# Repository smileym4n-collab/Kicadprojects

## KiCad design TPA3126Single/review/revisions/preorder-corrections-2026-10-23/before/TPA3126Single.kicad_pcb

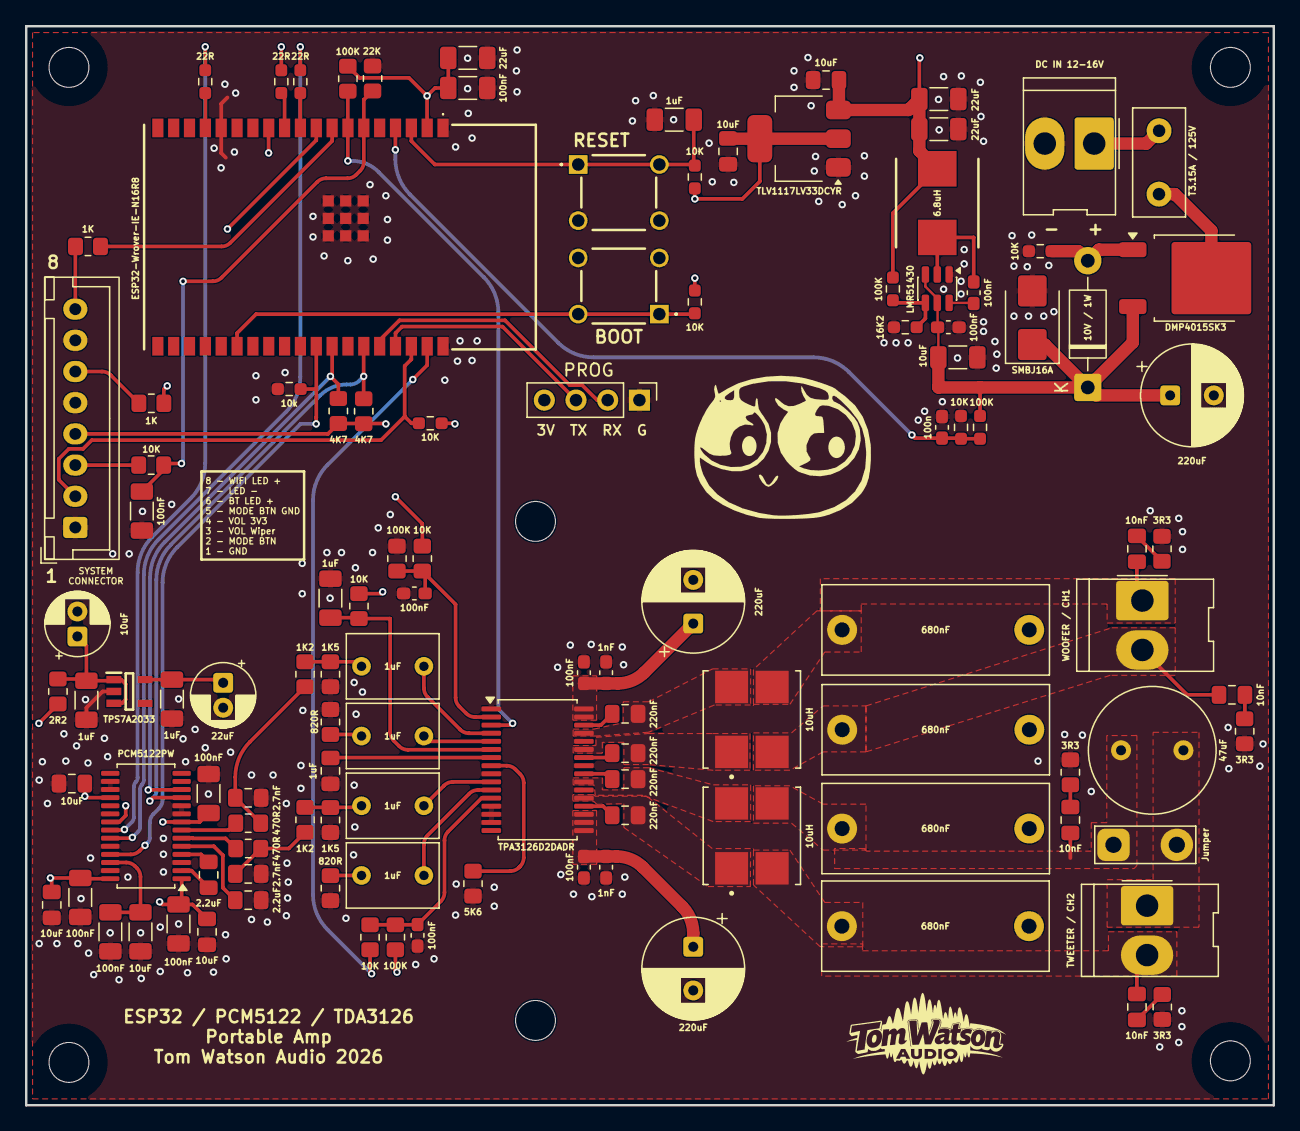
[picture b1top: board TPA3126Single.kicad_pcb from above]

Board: 4 copper layers, 100.0 x 86.5 mm, 120 parts (0 on the bottom side), 74 nets.

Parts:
C1, C2, C5, C6: 1uF; C_Rect_L7.2mm_W5.0mm_P5.00mm
C3, C11, C15, C17, C22, C58: 100nF; C_1206_3216Metric_Pad1.33x1.80mm_HandSolder
C4, C8, C9, C29: 1uF; C_1206_3216Metric_Pad1.33x1.80mm_HandSolder
C7: 10uF; CP_Radial_D5.0mm_P2.00mm
C10: 22uF; CP_Radial_D5.0mm_P2.00mm
C12, C14: 2.2uF; C_0805_2012Metric_Pad1.18x1.45mm_HandSolder
C13, C20, C23, C51, C52: 10uF; C_0805_2012Metric_Pad1.18x1.45mm_HandSolder
C16, C19: 2.7nF; C_0805_2012Metric_Pad1.18x1.45mm_HandSolder
C18, C45: 10uF; C_1206_3216Metric_Pad1.33x1.80mm_HandSolder
C21: 47uF; C_Radial_D10.0mm_H20.0mm_P5.00mm
C24, C25, C26, C27: 220nF; C_0805_2012Metric_Pad1.18x1.45mm_HandSolder
C28: 1uF; C_0805_2012Metric_Pad1.18x1.45mm_HandSolder
C30, C31, C33, C34, C46, C48: 100nF; C_0603_1608Metric_Pad1.08x0.95mm_HandSolder
C32, C54, C59, C60: 10nF; C_0805_2012Metric_Pad1.18x1.45mm_HandSolder
C35, C36, C47: 220uF; CP_Radial_D8.0mm_P3.50mm
C37, C38, C39, C40: 680nF; C_Rect_L18.0mm_W7.0mm_P15.00mm_FKS3_FKP3
C49, C50, C55: 22uF; C_1206_3216Metric_Pad1.33x1.80mm_HandSolder
C53: 100n; C_0603_1608Metric_Pad1.08x0.95mm_HandSolder
C56, C57: 1nF; C_0603_1608Metric_Pad1.08x0.95mm_HandSolder
D1: 10V / 1W; D_DO-41_SOD81_P10.16mm_Horizontal
D2: SMBJ16A; D_SMB
F2: T3.15A / 125V; Fuse_Littelfuse_395Series
H1, H2, H3, H4: MountingHole; MountingHole_3.2mm_M3
HS1: Heatsink; Heatsink_ATS_ATS-TI1OP-521-C1-R1_50x13.9mm_H25mm_P40mm
IC2: RESET; TS026650BK100SCRD
IC3: BOOT; TS026650BK100SCRD
IC4: TPS7A2033; SOT95P280X145-5N
IC5: ESP32-Wrover-IE-N16R8; ESP32-WROVER-IE-N16R8
J1: DC IN 12-16V; Molex_KK-396_5273-02A_1x02_P3.96mm_Vertical
J2: SYSTEM CONNECTOR; JST_XH_B8B-XH-A_1x08_P2.50mm_Vertical
J3: PROG; PinHeader_1x04_P2.54mm_Vertical
J16: WOOFER / CH1; Molex_KK-396_5273-02A_1x02_P3.96mm_Vertical
J17: TWEETER / CH2; Molex_KK-396_5273-02A_1x02_P3.96mm_Vertical
JP1: Jumper; TestPoint_2Pads_Pitch5.08mm_Drill1.3mm
L1: 6.8uH; SRP6030WA-6R8M
L2, L3: 10uH; CSAD0660-100M
Q1: DMP4015SK3; TO-252-2
R1: 2R2; R_0805_2012Metric_Pad1.20x1.40mm_HandSolder
R2, R3: 470R; R_0805_2012Metric_Pad1.20x1.40mm_HandSolder
R4, R5, R9: 22R; R_0603_1608Metric_Pad0.98x0.95mm_HandSolder
R6, R20, R34, R40: 3R3; R_0805_2012Metric_Pad1.20x1.40mm_HandSolder
R7, R8: 1K; R_0805_2012Metric_Pad1.20x1.40mm_HandSolder
R10, R11, R22, R28, R35: 10K; R_0603_1608Metric_Pad0.98x0.95mm_HandSolder
R12, R14: 1K2; R_0805_2012Metric_Pad1.20x1.40mm_HandSolder
R13, R15: 1K5; R_0805_2012Metric_Pad1.20x1.40mm_HandSolder
R16, R17: 820R; R_0805_2012Metric_Pad1.20x1.40mm_HandSolder
R18: 5K6; R_0805_2012Metric_Pad1.20x1.40mm_HandSolder
R19, R21, R26, R39: 10K; R_0805_2012Metric_Pad1.20x1.40mm_HandSolder
R23, R27: 100K; R_0603_1608Metric_Pad0.98x0.95mm_HandSolder
R24: 16K2; R_0603_1608Metric_Pad0.98x0.95mm_HandSolder
R25, R29, R30: 100K; R_0805_2012Metric_Pad1.20x1.40mm_HandSolder
R31, R33: 4K7; R_0805_2012Metric_Pad1.20x1.40mm_HandSolder
R32: 10k; R_0603_1608Metric_Pad0.98x0.95mm_HandSolder
R41: 22K; R_0805_2012Metric_Pad1.20x1.40mm_HandSolder
U1: TPA3126D2DADR; Texas_DAD0032A_HTSSOP-32_6.1x11mm_P0.65mm_TopEP3.71x3.81mm
U2: PCM5122PW; TSSOP-28_4.4x9.7mm_P0.65mm
U3: LMR51430; TSOT-23-6
U4: TLV1117LV33DCYR; SOT-223-3_TabPin2

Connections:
/3V3-ESP: C3.1, C52.1, C55.1, IC5.2 (3V3), J2.4, J3.4, R10.1, R11.1, R19.1, R29.1, R30.1, R31.1, R33.1, R35.2, U4.2 (VO)
/4V_PRE: C49.1, C50.1, C51.1, L1.2, R1.1, R23.1, U4.3 (VI)
/AMP/AMP_ENABLE: IC5.12 (IO27), R21.1
/AMP/AMP_FAULT_N: IC5.7 (IO35), R30.2, U1.3 (FAULTZ)
/AMP/AMP_LINN: C5.2, U1.11 (LINN)
/AMP/AMP_LINP: C6.2, U1.10 (LINP)
/AMP/AMP_MUTE: C31.1, R26.2, R29.2, U1.12 (MUTE)
/AMP/AMP_MUTE_CMD: IC5.37 (IO23), R26.1
/AMP/AMP_RINN: C2.2, U1.5 (RINN)
/AMP/AMP_RINP: C1.2, U1.4 (RINP)
/AMP/AMP_SDZ: C30.1, R21.2, R25.1, U1.2 (SDZ)
/AMP/GAIN_SLV: R18.1, U1.8 (GAIN_SLV)
/AMP/GVDD: C28.1, U1.7 (GVDD)
/AMP/PLIMIT: C29.1, R19.2, U1.6 (PLIMIT)
/AMP/SW_TN: C27.2, L3.1, U1.21 (OUTNL)
/AMP/SW_TP: C26.2, L3.4, U1.23 (OUTPL)
/AMP/SW_WN: C25.2, L2.1, U1.27 (OUTNR)
/AMP/SW_WP: C24.2, L2.4, U1.29 (OUTPR)
/AMP/TWEETER_AUDIO: C16.1, R2.2, R14.1
/AMP/TW_FILTER_P: C21.1, C39.2, C60.1, JP1.1 (A), L3.3
/AMP/TW_PROTECTED_P: C21.2, J17.1, JP1.2 (B)
/AMP/WOOFER_AUDIO: C19.1, R3.1, R12.1
/DAC/AVDD: C9.1, C10.1, C11.1, C13.1, C17.1, C20.1, C22.1, C23.1, IC4.5 (OUT), U2.1 (CPVDD), U2.8 (AVDD), U2.18 (MODE2/MS), U2.28 (DVDD)
/DAC/BCK: R5.1, U2.21 (BCK)
/DAC/DAC_XSMT: IC5.30 (IO18), R32.1, U2.25 (XSMT)
/DAC/DATA: R9.1, U2.22 (DIN)
/DAC/LRCK: R4.1, U2.23 (LRCK)
/ESP32/BT_LED: J2.6, R7.1
/ESP32/EN: C4.1, IC2.1 (NO_1), IC2.2 (NO_2), IC5.3 (EN), R10.2
/ESP32/GPIO0: IC3.1 (NO_1), IC3.2 (NO_2), IC5.25 (IO0), R11.2
/ESP32/MODE BTN: IC5.36 (IO22), J2.2, R35.1
/ESP32/RX: IC5.34 (RXD0), J3.2
/ESP32/SCL: IC5.31 (IO19), R31.2, U2.12 (SCL/MC/ATT1)
/ESP32/SDA: IC5.33 (IO21), R33.2, U2.11 (SDA/MOSI/ATT2)
/ESP32/TX: IC5.35 (TXD0), J3.3
/ESP32/VOL-ADC: C58.1, IC5.6 (IO34), R39.2, R41.1
/ESP32/WIFI_LED: J2.8, R8.1
/PVDD: C33.1, C34.1, C35.1, C36.1, C45.1, C46.1, C47.1, C56.1, C57.1, D1.1 (K), D2.1 (K), Q1.3 (S), R27.1, U1.17 (AVCC), U1.18 (PVCC), U1.19 (PVCC), U1.31 (PVCC), U1.32 (PVCC), U3.3 (VIN), U3.5 (EN)
/VIN_SENSE: C53.1, IC5.4 (SENSOR_VP), R27.2, R28.1
GND: C3.2, C4.2, C7.2, C8.2, C9.2, C10.2, C11.2, C12.2, C13.2, C15.2, C16.2, C17.2, C18.2, C19.2, C20.2, C22.2, C23.2, C28.2, C29.2, C30.2, C31.2, C33.2, C34.2, C35.2, C36.2, C37.1, C38.2, C39.1, C40.2, C45.2, C46.2, C47.2, C49.2, C50.2, C51.2, C52.2, C53.2, C55.2, C56.2, C57.2, C58.2, D2.2 (A), IC2.3 (COM_1), IC2.4 (COM_2), IC3.3 (COM_1), IC3.4 (COM_2), IC4.2 (GND), IC5.1 (GND_1), IC5.15 (GND_2), IC5.38 (GND_3), IC5.39 (GND_4), IC5.40 (GND_5), IC5.41 (GND_6), IC5.42 (GND_7), IC5.43 (GND_8), IC5.44 (GND_9), IC5.45 (GND_10), IC5.46 (GND_11), IC5.47 (GND_12), J1.2, J2.1, J2.5, J2.7, J3.1, R6.2, R13.1, R15.1, R16.1, R17.1, R18.2, R20.2, R22.2, R24.2, R25.2, R28.2, R32.2, R34.2, R40.2, R41.2, U1.1 (MODSEL), U1.9 (GND), U1.13 (AM2), U1.14 (AM1), U1.15 (AM0), U1.22 (GND), U1.25 (GND), U1.28 (GND), U2.3 (CPGND), U2.9 (AGND), U2.10 (VCOM/DEMP), U2.16 (ADR2/GPIO2/DOUT), U2.17 (MODE1), U2.20 (SCK), U2.24 (ADR1/MISO/FMT), U2.27 (DGND), U3.1 (GND), U4.1 (GND)
unnamed: C1.1, R12.2, R13.2
unnamed: C2.1, R16.2
unnamed: C5.1, R17.2
unnamed: C6.1, R14.2, R15.2
unnamed: C32.2, R6.1
unnamed: C54.2, R20.1
unnamed: C59.2, R34.1
unnamed: C60.2, R40.1
unnamed: D1.2 (A), Q1.1 (G), R22.1
unnamed: C7.1, C8.1, IC4.1 (IN), IC4.3 (EN), R1.2
unnamed: IC5.16 (IO13), R9.2
unnamed: IC5.10 (IO25), R4.2
unnamed: IC5.11 (IO26), R5.2
unnamed: IC5.8 (IO32), R8.2
unnamed: IC5.9 (IO33), R7.2
unnamed: F2.1, J1.1
unnamed: J2.3, R39.1
unnamed: C37.2, C54.1, J16.1, L2.3
unnamed: C32.1, C38.1, J16.2, L2.2
unnamed: C40.1, C59.1, J17.2, L3.2
unnamed: F2.2, Q1.2 (D)
unnamed: C27.1, U1.20 (BSNL)
unnamed: C25.1, U1.26 (BSNR)
unnamed: C26.1, U1.24 (BSPL)
unnamed: C24.1, U1.30 (BSPR)
unnamed: C14.2, U2.4 (CAPM)
unnamed: C14.1, U2.2 (CAPP)
unnamed: C15.1, C18.1, U2.26 (LDOO)
unnamed: R2.1, U2.6 (OUTL)
unnamed: R3.2, U2.7 (OUTR)
unnamed: C12.1, U2.5 (VNEG)
unnamed: C48.1, U3.6 (CB)
unnamed: R23.2, R24.1, U3.4 (FB)
unnamed: C48.2, L1.1, U3.2 (SW)

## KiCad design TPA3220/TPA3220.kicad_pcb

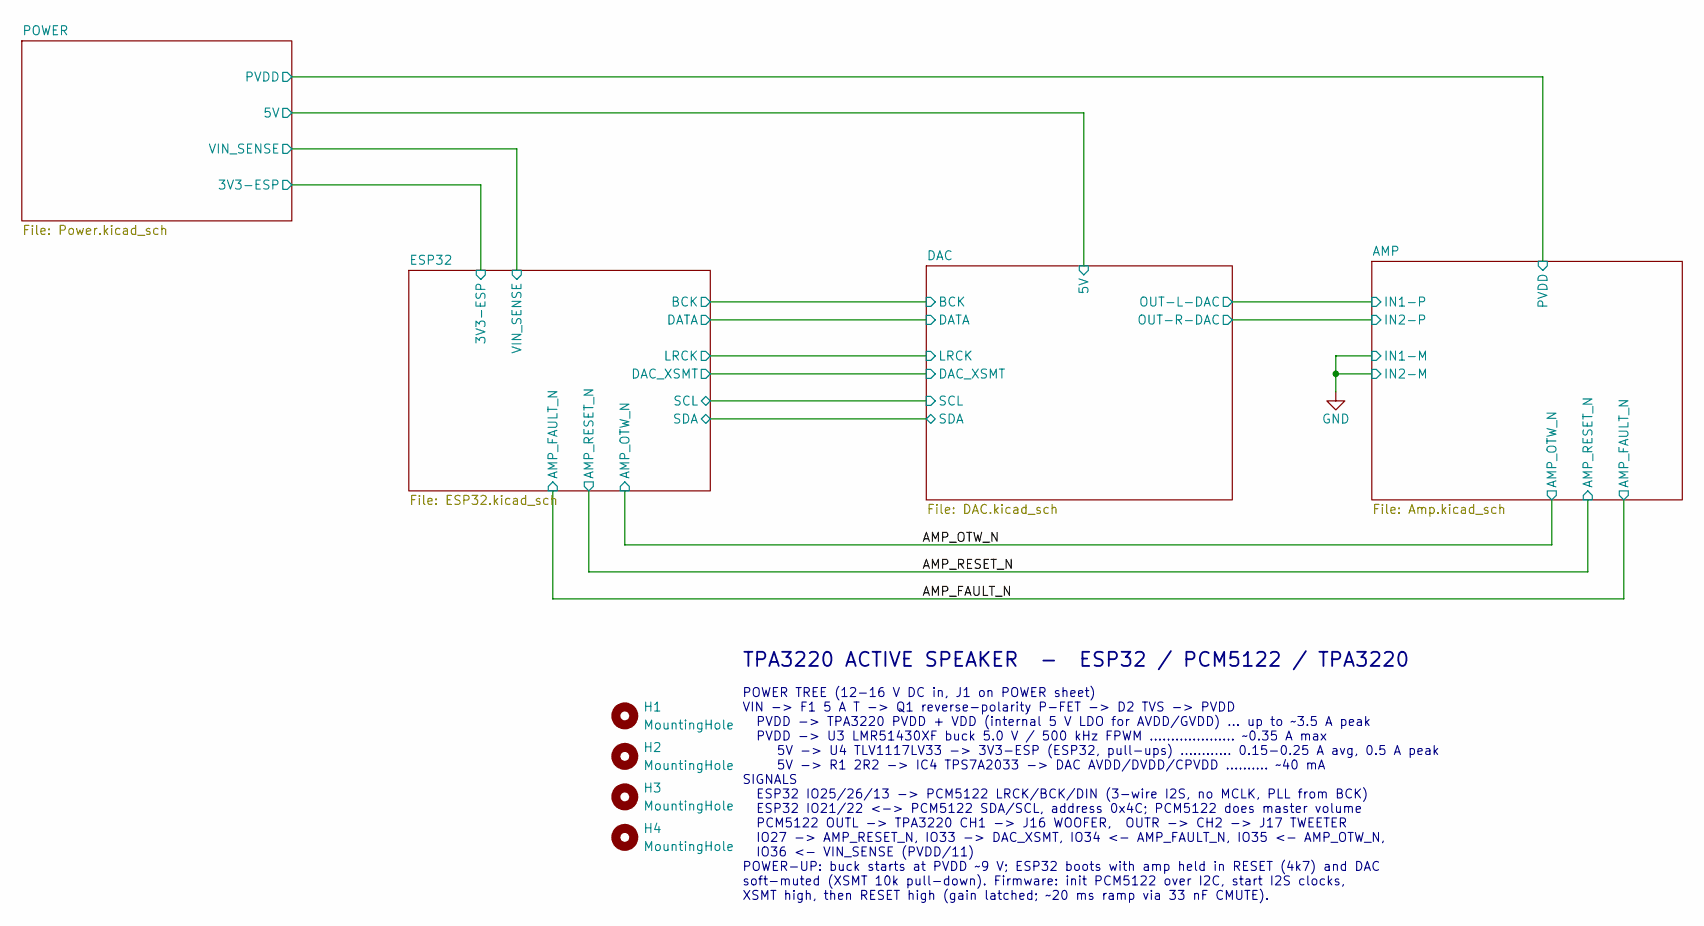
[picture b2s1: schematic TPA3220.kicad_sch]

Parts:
H1, H2, H3, H4: MountingHole; MountingHole_3.2mm_M3

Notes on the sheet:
TPA3220 ACTIVE SPEAKER - ESP32 / PCM5122 / TPA3220
POWER TREE (12-16 V DC in, J1 on POWER sheet) VIN -> F1 5 A T -> Q1 reverse-polarity P-FET -> D2 TVS -> PVDD PVDD -> TPA3220 PVDD + VDD (internal 5 V LDO for AVDD/GVDD) ... up to ~3.5 A peak PVDD -> U3 LMR51430XF buck 5.0 V / 500 kHz FPWM .................... ~0.35 A max 5V -> U4 TLV1117LV33 -> 3V3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

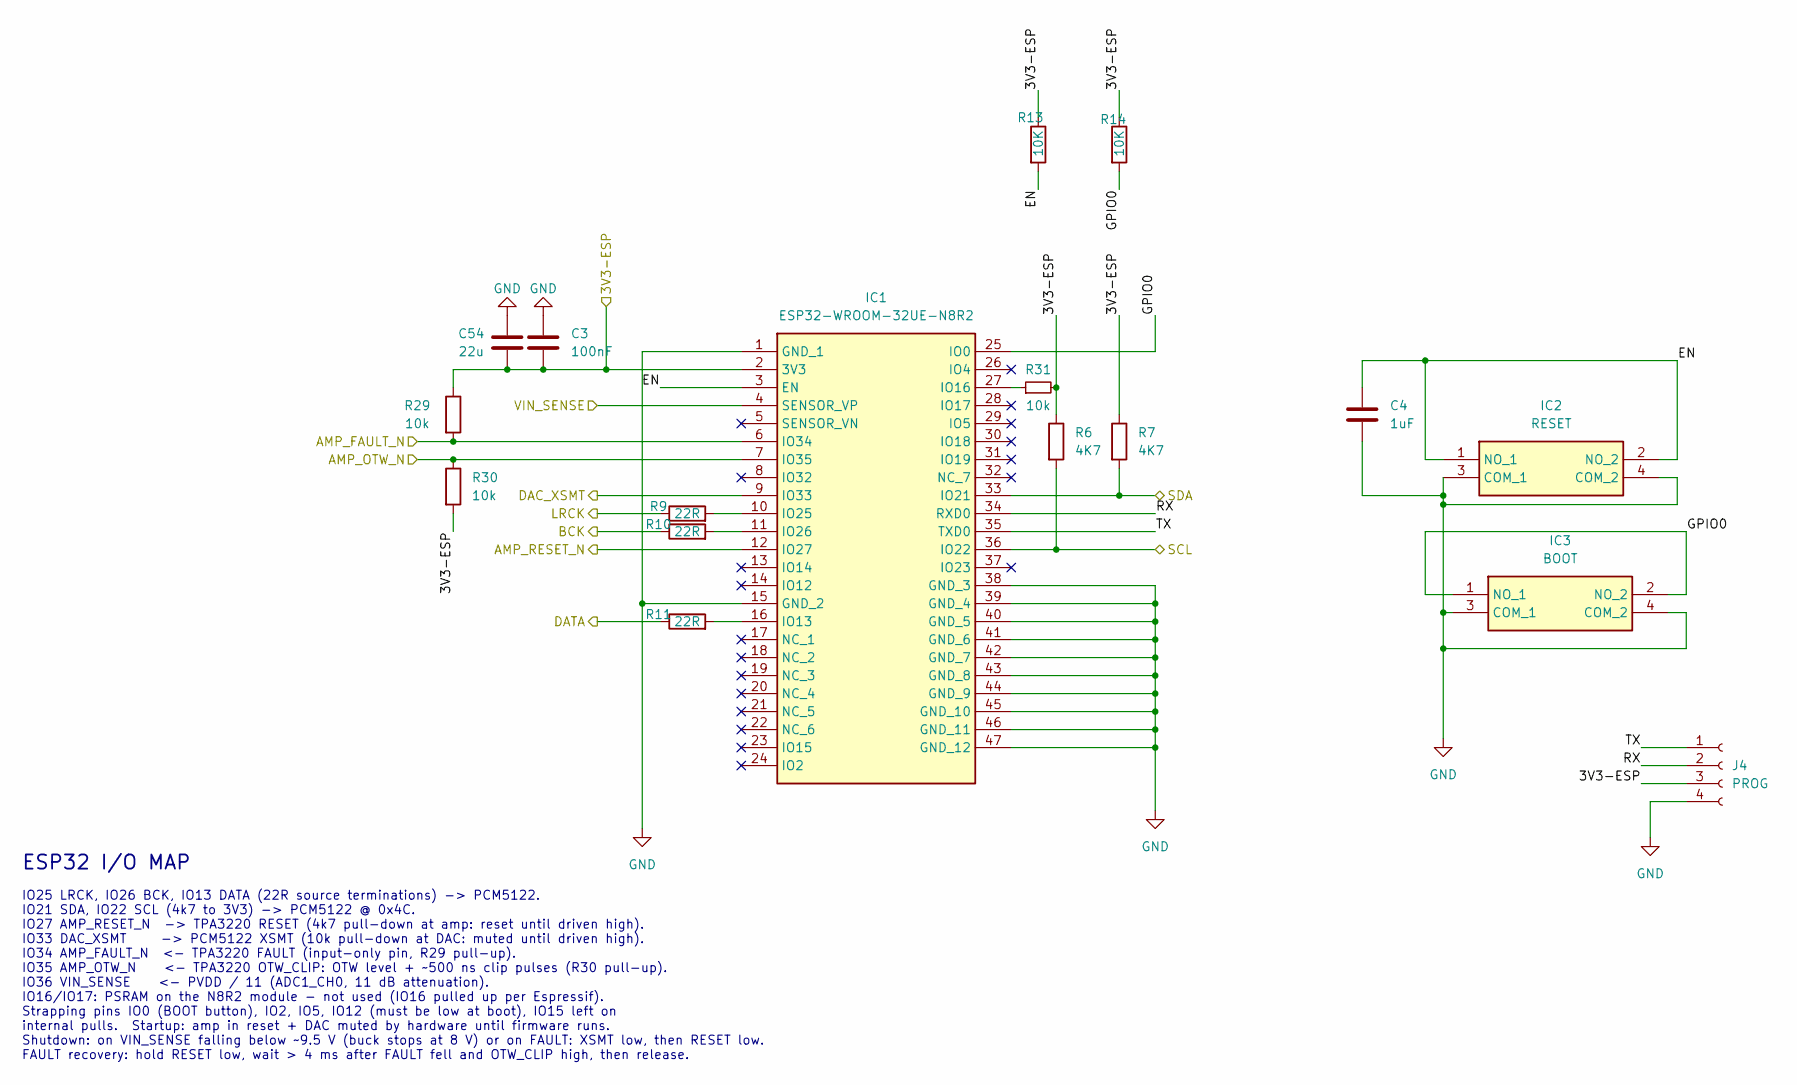
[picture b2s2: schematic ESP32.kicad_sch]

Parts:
C3: 100nF; C_1206_3216Metric_Pad1.33x1.80mm_HandSolder
C4: 1uF; C_1206_3216Metric_Pad1.33x1.80mm_HandSolder
C54: 22u; C_1206_3216Metric_Pad1.33x1.80mm_HandSolder; Manufacturer_Part_Number GRM31CR61E226KE15L
IC1: ESP32-WROOM-32UE-N8R2; ESP32WROOM32UEN8R2; Mouser Part Number 356-ESP32WRM32UEN8R2
IC2: RESET; TS026650BK100SCRD; Mouser Part Number 179-TS026650BK100SCR
IC3: BOOT; TS026650BK100SCRD; Mouser Part Number 179-TS026650BK100SCR
J4: PROG; PinHeader_1x04_P2.54mm_Vertical
R6, R7: 4K7; R_0805_2012Metric_Pad1.20x1.40mm_HandSolder
R9, R10, R11: 22R; R_0603_1608Metric_Pad0.98x0.95mm_HandSolder
R13, R14: 10K; R_0603_1608Metric_Pad0.98x0.95mm_HandSolder
R29, R30, R31: 10k; R_0603_1608Metric_Pad0.98x0.95mm_HandSolder; Manufacturer_Part_Number RC0603FR-0710KL

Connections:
/AMP_FAULT_N: IC1.6 (IO34), R29.2; also elsewhere on the board
/AMP_OTW_N: IC1.7 (IO35), R30.1; also elsewhere on the board
/AMP_RESET_N: IC1.12 (IO27); also elsewhere on the board
/DAC/BCK: R10.1; also elsewhere on the board
/DAC/DAC_XSMT: IC1.9 (IO33); also elsewhere on the board
/DAC/DATA: R11.1; also elsewhere on the board
/DAC/LRCK: R9.1; also elsewhere on the board
/DAC/SCL: IC1.36 (IO22), R6.2; also elsewhere on the board
/DAC/SDA: IC1.33 (IO21), R7.2; also elsewhere on the board
/ESP32/3V3-ESP: C3.2, C54.2, IC1.2 (3V3), J4.3, R6.1, R7.1, R13.1, R14.1, R29.1, R30.2, R31.2; also elsewhere on the board
/ESP32/EN: C4.1, IC1.3 (EN), IC2.1 (NO_1), IC2.2 (NO_2), R13.2
/ESP32/GPIO0: IC1.25 (IO0), IC3.1 (NO_1), IC3.2 (NO_2), R14.2
/ESP32/RX: IC1.34 (RXD0), J4.2
/ESP32/TX: IC1.35 (TXD0), J4.1
/ESP32/VIN_SENSE: IC1.4 (SENSOR_VP); also elsewhere on the board
GND: C3.1, C4.2, C54.1, IC1.1 (GND_1), IC1.15 (GND_2), IC1.38 (GND_3), IC1.39 (GND_4), IC1.40 (GND_5), IC1.41 (GND_6), IC1.42 (GND_7), IC1.43 (GND_8), IC1.44 (GND_9), IC1.45 (GND_10), IC1.46 (GND_11), IC1.47 (GND_12), IC2.3 (COM_1), IC2.4 (COM_2), IC3.3 (COM_1), IC3.4 (COM_2), J4.4; also elsewhere on the board
unnamed: IC1.16 (IO13), R11.2
unnamed: IC1.27 (IO16), R31.1
unnamed: IC1.10 (IO25), R9.2
unnamed: IC1.11 (IO26), R10.2

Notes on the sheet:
ESP32 I/O MAP
IO25 LRCK, IO26 BCK, IO13 DATA (22R source terminations) -> PCM5122. IO21 SDA, IO22 SCL (4k7 to 3V3) -> PCM5122 @ 0x4C. IO27 AMP_RESET_N -> TPA3220 RESET (4k7 pull-down at amp: reset until driven high). IO33 DAC_XSMT -> PCM5122 XSMT (10k pull-down at DAC: muted until driven high). IO34 AMP_FAULT_N 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

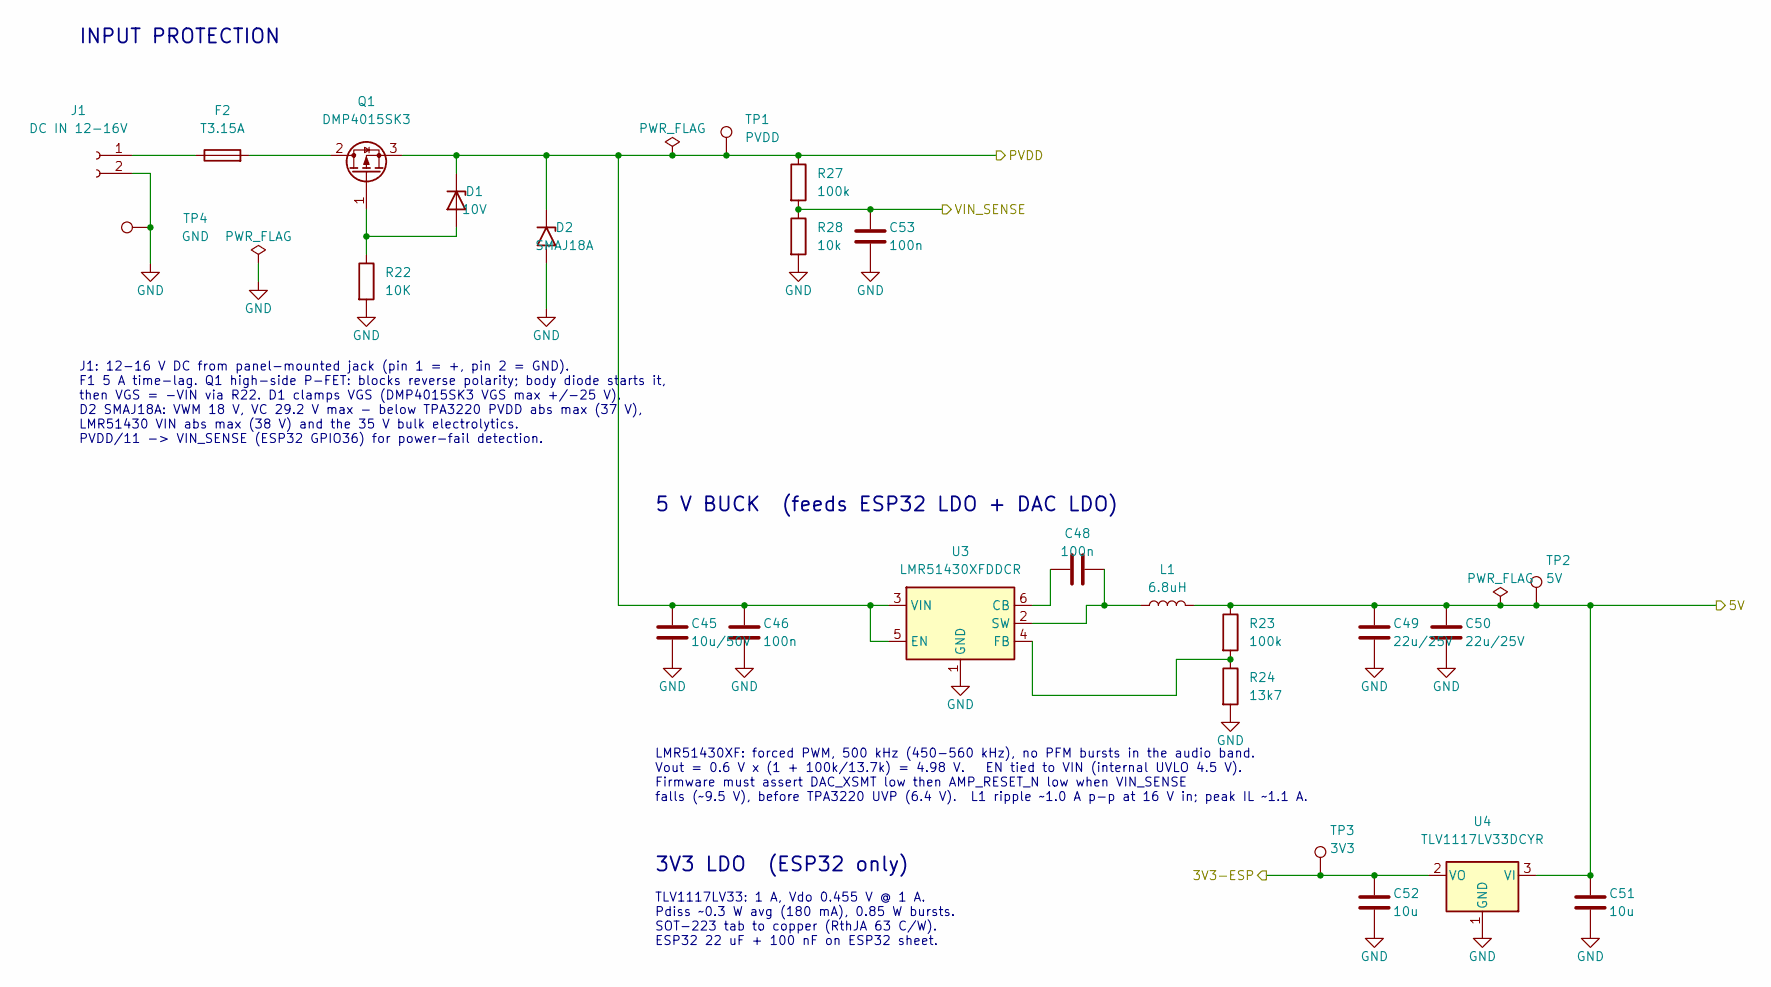
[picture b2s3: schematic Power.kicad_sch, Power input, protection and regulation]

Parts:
C45: 10u/50V; C_1210_3225Metric_Pad1.33x2.70mm_HandSolder; Manufacturer_Part_Number GRM32ER71H106KA12L
C46, C48, C53: 100n; C_0603_1608Metric_Pad1.08x0.95mm_HandSolder; Manufacturer_Part_Number C0603C104M5RACTU
C49, C50: 22u/25V; C_1206_3216Metric_Pad1.33x1.80mm_HandSolder; Manufacturer_Part_Number GRM31CR61E226KE15L
C51, C52: 10u; C_0805_2012Metric_Pad1.18x1.45mm_HandSolder; Manufacturer_Part_Number CL21A106KOQNNNE
D1: 10V; D_DO-41_SOD81_P10.16mm_Horizontal; Manufacturer_Part_Number MMSZ5245BT1G
D2: SMAJ18A; D_SMA; Manufacturer_Part_Number SMAJ18A
F2: T3.15A; Fuse_Littelfuse_395Series
J1: DC IN 12-16V; Molex_KK-396_A-41791-0002_1x02_P3.96mm_Vertical; Manufacturer_Part_Number 0026604020
L1: 6.8uH; SRP6030WA-6R8M; Manufacturer_Part_Number SRP6030WA-6R8M
Q1: DMP4015SK3; TO-252-2; Manufacturer_Part_Number DMP4015SK3-13
R22: 10K; R_0603_1608Metric_Pad0.98x0.95mm_HandSolder; Manufacturer_Part_Number RC0603FR-0710KL
R23, R27: 100k; R_0603_1608Metric_Pad0.98x0.95mm_HandSolder; Manufacturer_Part_Number RC0603FR-07100KL
R24: 13k7; R_0603_1608Metric_Pad0.98x0.95mm_HandSolder; Manufacturer_Part_Number RC0603FR-0713K7L
R28: 10k; R_0603_1608Metric_Pad0.98x0.95mm_HandSolder; Manufacturer_Part_Number RC0603FR-0710KL
TP1: PVDD; TestPoint_Pad_D1.5mm
TP2: 5V; TestPoint_Pad_D1.5mm
TP3: 3V3; TestPoint_Pad_D1.5mm
TP4: GND; TestPoint_Pad_D1.5mm
U3: LMR51430XFDDCR; TSOT-23-6; Manufacturer_Part_Number LMR51430XFDDCR
U4: TLV1117LV33DCYR; SOT-223-3_TabPin2; Manufacturer_Part_Number TLV1117LV33DCYR

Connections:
/AMP/PVDD: C45.1, C46.1, D1.1 (K), D2.1 (A1), Q1.3 (S), R27.1, TP1.1 (1_1), U3.3 (VIN), U3.5 (EN); also elsewhere on the board
/DAC/5V: C49.1, C50.1, C51.1, L1.2, R23.1, TP2.1 (1_1), U4.3 (VI); also elsewhere on the board
/ESP32/3V3-ESP: C52.1, TP3.1 (1_1), U4.2 (VO); also elsewhere on the board
/ESP32/VIN_SENSE: C53.1, R27.2, R28.1; also elsewhere on the board
GND: C45.2, C46.2, C49.2, C50.2, C51.2, C52.2, C53.2, D2.2 (A2), J1.2, R22.2, R24.2, R28.2, TP4.1 (1_1), U3.1 (GND), U4.1 (GND); also elsewhere on the board
unnamed: D1.2 (A), Q1.1 (G), R22.1
unnamed: F2.1, J1.1
unnamed: F2.2, Q1.2 (D)
unnamed: C48.1, U3.6 (CB)
unnamed: R23.2, R24.1, U3.4 (FB)
unnamed: C48.2, L1.1, U3.2 (SW)

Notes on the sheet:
5 V BUCK (feeds ESP32 LDO + DAC LDO)
LMR51430XF: forced PWM, 500 kHz (450-560 kHz), no PFM bursts in the audio band. Vout = 0.6 V x (1 + 100k/13.7k) = 4.98 V. EN tied to VIN (internal UVLO 4.5 V). Firmware must assert DAC_XSMT low then AMP_RESET_N low when VIN_SENSE falls (~9.5 V), before TPA3220 UVP (6.4 V). L1 ripple ~1.0 A p-p at 1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
INPUT PROTECTION
3V3 LDO (ESP32 only)
J1: 12-16 V DC from panel-mounted jack (pin 1 = +, pin 2 = GND). F1 5 A time-lag. Q1 high-side P-FET: blocks reverse polarity; body diode starts it, then VGS = -VIN via R22. D1 clamps VGS (DMP4015SK3 VGS max +/-25 V). D2 SMAJ18A: VWM 18 V, VC 29.2 V max - below TPA3220 PVDD abs max (37 V), LMR51430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
TLV1117LV33: 1 A, Vdo 0.455 V @ 1 A. Pdiss ~0.3 W avg (180 mA), 0.85 W bursts. SOT-223 tab to copper (RthJA 63 C/W). ESP32 22 uF + 100 nF on ESP32 sheet.

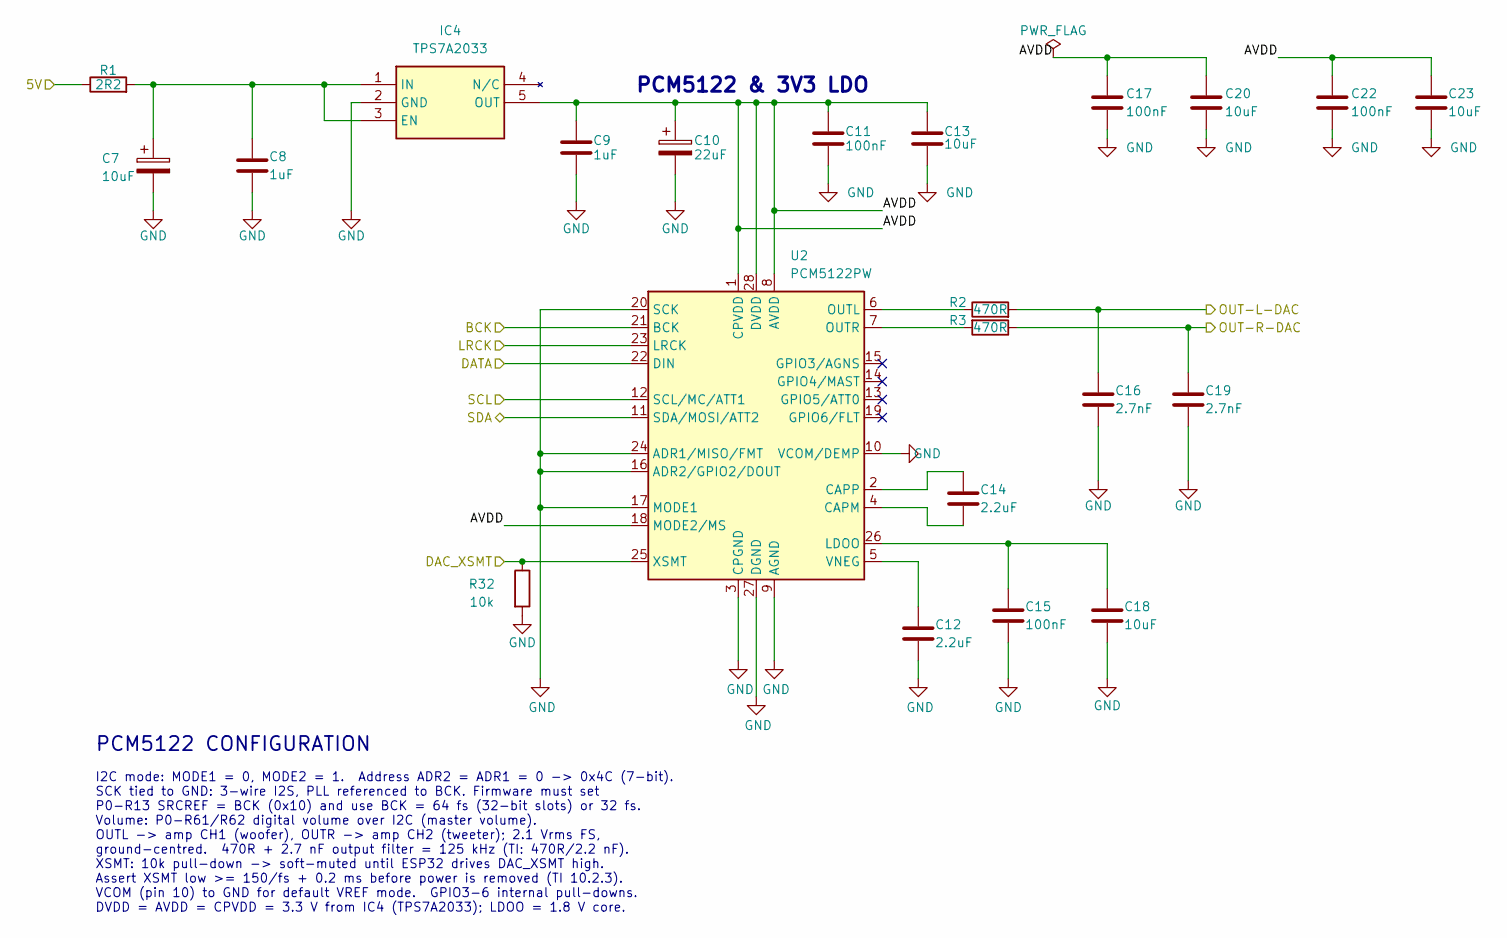
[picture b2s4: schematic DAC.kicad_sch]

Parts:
C7: 10uF; CP_Radial_D4.0mm_P1.50mm
C8, C9: 1uF; C_1206_3216Metric_Pad1.33x1.80mm_HandSolder
C10: 22uF; CP_Radial_D5.0mm_P2.50mm
C11, C15, C17, C22: 100nF; C_1206_3216Metric_Pad1.33x1.80mm_HandSolder
C12, C14: 2.2uF; C_0805_2012Metric_Pad1.18x1.45mm_HandSolder
C13, C20, C23: 10uF; C_0805_2012Metric_Pad1.18x1.45mm_HandSolder
C16, C19: 2.7nF; C_0805_2012Metric_Pad1.18x1.45mm_HandSolder
C18: 10uF; C_1206_3216Metric_Pad1.33x1.80mm_HandSolder
IC4: TPS7A2033; SOT95P280X145-5N; Mouser Part Number 595-TPS7A2033PDBVR
R1: 2R2; R_0805_2012Metric_Pad1.20x1.40mm_HandSolder
R2, R3: 470R; R_0805_2012Metric_Pad1.20x1.40mm_HandSolder
R32: 10k; R_0603_1608Metric_Pad0.98x0.95mm_HandSolder; Manufacturer_Part_Number RC0603FR-0710KL
U2: PCM5122PW; TSSOP-28_4.4x9.7mm_P0.65mm

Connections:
/AMP/IN1-P: C16.1, R2.2; also elsewhere on the board
/AMP/IN2-P: C19.1, R3.1; also elsewhere on the board
/DAC/5V: R1.1; also elsewhere on the board
/DAC/AVDD: C9.1, C10.1, C11.1, C13.1, C17.1, C20.1, C22.1, C23.1, IC4.5 (OUT), U2.1 (CPVDD), U2.8 (AVDD), U2.18 (MODE2/MS), U2.28 (DVDD)
/DAC/BCK: U2.21 (BCK); also elsewhere on the board
/DAC/DAC_XSMT: R32.1, U2.25 (XSMT); also elsewhere on the board
/DAC/DATA: U2.22 (DIN); also elsewhere on the board
/DAC/LRCK: U2.23 (LRCK); also elsewhere on the board
/DAC/SCL: U2.12 (SCL/MC/ATT1); also elsewhere on the board
/DAC/SDA: U2.11 (SDA/MOSI/ATT2); also elsewhere on the board
GND: C7.2, C8.2, C9.2, C10.2, C11.2, C12.2, C13.2, C15.2, C16.2, C17.2, C18.2, C19.2, C20.2, C22.2, C23.2, IC4.2 (GND), R32.2, U2.3 (CPGND), U2.9 (AGND), U2.10 (VCOM/DEMP), U2.16 (ADR2/GPIO2/DOUT), U2.17 (MODE1), U2.20 (SCK), U2.24 (ADR1/MISO/FMT), U2.27 (DGND); also elsewhere on the board
unnamed: C7.1, C8.1, IC4.1 (IN), IC4.3 (EN), R1.2
unnamed: C14.2, U2.4 (CAPM)
unnamed: C14.1, U2.2 (CAPP)
unnamed: C15.1, C18.1, U2.26 (LDOO)
unnamed: R2.1, U2.6 (OUTL)
unnamed: R3.2, U2.7 (OUTR)
unnamed: C12.1, U2.5 (VNEG)

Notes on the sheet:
PCM5122 & 3V3 LDO
PCM5122 CONFIGURATION
I2C mode: MODE1 = 0, MODE2 = 1. Address ADR2 = ADR1 = 0 -> 0x4C (7-bit). SCK tied to GND: 3-wire I2S, PLL referenced to BCK. Firmware must set P0-R13 SRCREF = BCK (0x10) and use BCK = 64 fs (32-bit slots) or 32 fs. Volume: P0-R61/R62 digital volume over I2C (master volume). OUTL -> amp CH1 (woofer)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

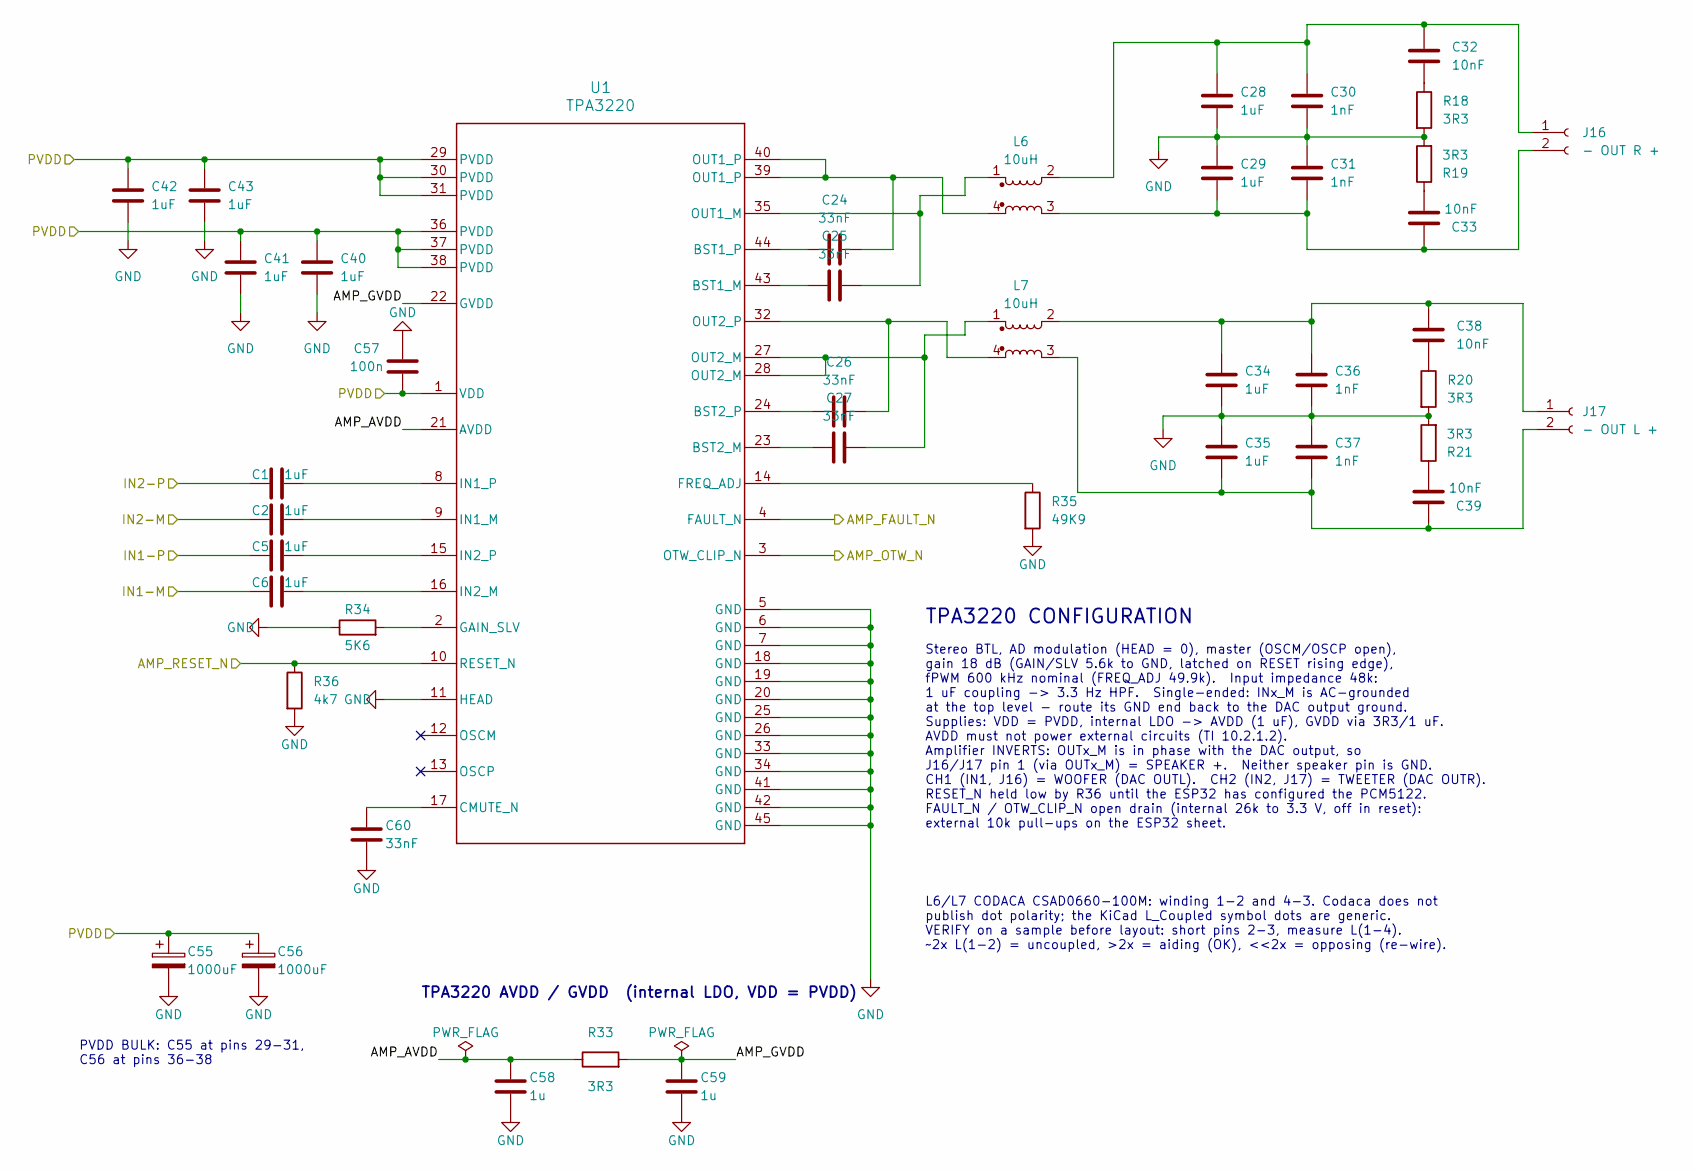
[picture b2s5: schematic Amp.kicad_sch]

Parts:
C1, C2, C5, C6, C28, C29, C34, C35: 1uF; C_Rect_L7.2mm_W5.5mm_P5.00mm_FKS2_FKP2_MKS2_MKP2
C24, C25, C26, C27: 33nF; C_0805_2012Metric_Pad1.18x1.45mm_HandSolder
C30, C31, C36, C37: 1nF; C_0805_2012Metric_Pad1.18x1.45mm_HandSolder
C32, C33, C38, C39: 10nF; C_0805_2012Metric_Pad1.18x1.45mm_HandSolder
C40, C41, C42, C43: 1uF; C_0603_1608Metric_Pad1.08x0.95mm_HandSolder
C55, C56: 1000uF; CP_Radial_D12.5mm_P5.00mm; Manufacturer_Part_Number EEU-FR1V471
C57: 100n; C_0603_1608Metric_Pad1.08x0.95mm_HandSolder; Manufacturer_Part_Number C0603C104M5RACTU
C58, C59: 1u; C_1206_3216Metric_Pad1.33x1.80mm_HandSolder; Manufacturer_Part_Number CL21B105KAFNNNG
C60: 33nF; C_0805_2012Metric_Pad1.18x1.45mm_HandSolder; Manufacturer_Part_Number C0603C333K5RACTU
J16: - OUT R +; Molex_KK-396_A-41791-0002_1x02_P3.96mm_Vertical
J17: - OUT L +; Molex_KK-396_A-41791-0002_1x02_P3.96mm_Vertical
L6, L7: 10uH; CSAD0660-100M
R18, R19, R20, R21: 3R3; R_2512_6332Metric_Pad1.40x3.35mm_HandSolder
R33: 3R3; R_2512_6332Metric_Pad1.40x3.35mm_HandSolder; Manufacturer_Part_Number RC0603FR-073R3L
R34: 5K6; R_0805_2012Metric_Pad1.20x1.40mm_HandSolder; Manufacturer_Part_Number RC0603FR-075K6L
R35: 49K9; R_0805_2012Metric_Pad1.20x1.40mm_HandSolder; Manufacturer_Part_Number RC0603FR-0749K9L
R36: 4k7; R_0805_2012Metric_Pad1.20x1.40mm_HandSolder; Manufacturer_Part_Number RC0603FR-074K7L
U1: TPA3220; TPA3220_DDW0044D_HTSSOP-44_6.1x14mm_P0.635mm_EP5.2x14mm_Mas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

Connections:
/AMP/AMP_AVDD: C58.1, R33.1, U1.21 (AVDD)
/AMP/AMP_GVDD: C59.1, R33.2, U1.22 (GVDD)
/AMP/IN1-P: C5.1; also elsewhere on the board
/AMP/IN2-P: C1.1; also elsewhere on the board
/AMP/PVDD: C40.1, C41.1, C42.1, C43.1, C55.1, C56.1, C57.2, U1.1 (VDD), U1.29 (PVDD), U1.30 (PVDD), U1.31 (PVDD), U1.36 (PVDD), U1.37 (PVDD), U1.38 (PVDD); also elsewhere on the board
/AMP_FAULT_N: U1.4 (FAULT_N); also elsewhere on the board
/AMP_OTW_N: U1.3 (OTW_CLIP_N); also elsewhere on the board
/AMP_RESET_N: R36.1, U1.10 (RESET_N); also elsewhere on the board
GND: C2.1, C6.1, C28.2, C29.1, C30.1, C31.2, C34.2, C35.1, C36.1, C37.2, C40.2, C41.2, C42.2, C43.2, C55.2, C56.2, C57.1, C58.2, C59.2, C60.2, R18.2, R19.2, R20.2, R21.2, R34.1, R35.2, R36.2, U1.5 (GND), U1.6 (GND), U1.7 (GND), U1.11 (HEAD), U1.18 (GND), U1.19 (GND), U1.20 (GND), U1.25 (GND), U1.26 (GND), U1.33 (GND), U1.34 (GND), U1.41 (GND), U1.42 (GND), U1.45 (GND); also elsewhere on the board
unnamed: C24.2, L6.4, U1.39 (OUT1_P), U1.40 (OUT1_P)
unnamed: C27.2, L7.1, U1.27 (OUT2_M), U1.28 (OUT2_M)
unnamed: C32.1, R18.1
unnamed: C33.1, R19.1
unnamed: C38.1, R20.1
unnamed: C39.1, R21.1
unnamed: C28.1, C30.2, C32.2, J16.1, L6.2
unnamed: C29.2, C31.1, C33.2, J16.2, L6.3
unnamed: C34.1, C36.2, C38.2, J17.1, L7.2
unnamed: C35.2, C37.1, C39.2, J17.2, L7.3
unnamed: C25.1, U1.43 (BST1_M)
unnamed: C24.1, U1.44 (BST1_P)
unnamed: C27.1, U1.23 (BST2_M)
unnamed: C26.1, U1.24 (BST2_P)
unnamed: C60.1, U1.17 (CMUTE_N)
unnamed: R35.1, U1.14 (FREQ_ADJ)
unnamed: R34.2, U1.2 (GAIN_SLV)
unnamed: C2.2, U1.9 (IN1_M)
unnamed: C1.2, U1.8 (IN1_P)
unnamed: C6.2, U1.16 (IN2_M)
unnamed: C5.2, U1.15 (IN2_P)
unnamed: C25.2, L6.1, U1.35 (OUT1_M)
unnamed: C26.2, L7.4, U1.32 (OUT2_P)

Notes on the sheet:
L6/L7 CODACA CSAD0660-100M: winding 1-2 and 4-3. Codaca does not publish dot polarity; the KiCad L_Coupled symbol dots are generic. VERIFY on a sample before layout: short pins 2-3, measure L(1-4). ~2x L(1-2) = uncoupled, >2x = aiding (OK), <<2x = opposing (re-wire).
Stereo BTL, AD modulation (HEAD = 0), master (OSCM/OSCP open), gain 18 dB (GAIN/SLV 5.6k to GND, latched on RESET rising edge), fPWM 600 kHz nominal (FREQ_ADJ 49.9k). Input impedance 48k: 1 uF coupling -> 3.3 Hz HPF. Single-ended: INx_M is AC-grounded at the top level - route its GND end back to th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
PVDD BULK: C55 at pins 29-31, C56 at pins 36-38
TPA3220 CONFIGURATION
TPA3220 AVDD / GVDD (internal LDO, VDD = PVDD)

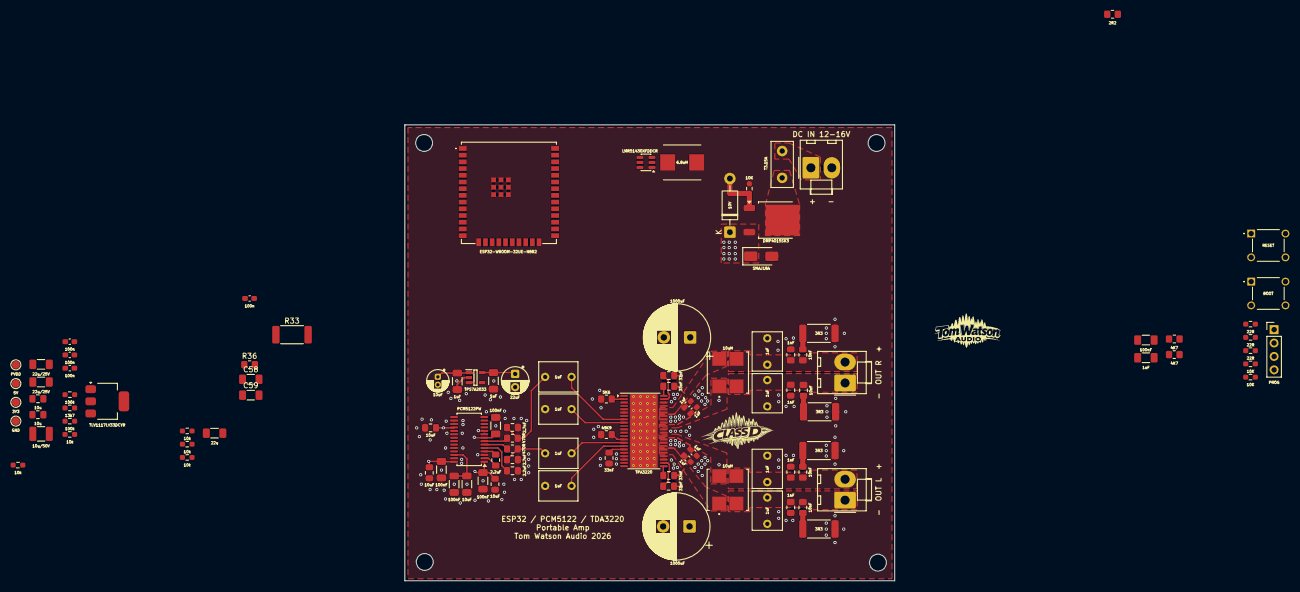
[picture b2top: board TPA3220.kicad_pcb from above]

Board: 4 copper layers, 92.8 x 86.4 mm, 111 parts (0 on the bottom side), 63 nets.
